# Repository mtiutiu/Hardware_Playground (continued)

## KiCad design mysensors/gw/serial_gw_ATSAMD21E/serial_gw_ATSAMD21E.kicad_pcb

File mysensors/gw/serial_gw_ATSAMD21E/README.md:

## Mysensors RFM69W Serial Gateway(ATSAMD21E)

**IMPORTANT NOTICE: this project proved not to work - Found the issue - VDDCORE was tied to the 3.3V supply rail by accident! - Fixed in REV 0.5**

##### 3D renderings of pcb

Top view | Bottom view
------------ | -------------
 | 

**Description:**

This is a Mysensors serial GW using **RFM69W** radio module and **ATSAMD21E** 32 bit MCU 

**Key features:**

 - **ATSHA204A** for signing
 - **MySensors** ready(ATSAMD21E + RFM69W)

**Work progress:**
 1. Test/verify the pcb board correctness(from both electrical and mechanical point of views) - **DONE**
 2. Produce the initial PCB's using some external PCB manufacturer - **IN PROGRESS**
 3. Components assembly(soldering)
 4. Upload Mysensors serial GW sketch code
 5. Verify the real board with running code
 6. Create project enclosure using a 3D printer

**HW Revisions:**
 - 0.1 - initial design
 - 0.2 - added I2C EEPROM and VUSB filtering caps
 - 0.3 - added USB lines termination resistors
 - 0.4 - added I2C EEPROM pull-up resistors
 - 0.5 - fixed VDDCORE mistake

**Credits:**
  
  All credits go to **MySensors** team for the great work and to the opensource community

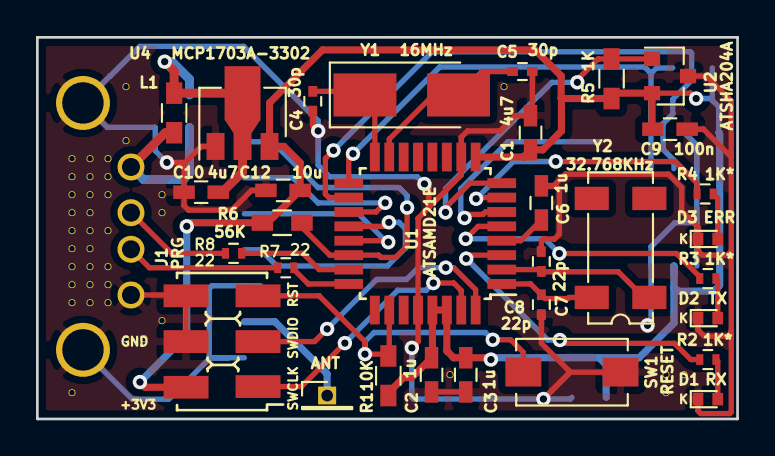
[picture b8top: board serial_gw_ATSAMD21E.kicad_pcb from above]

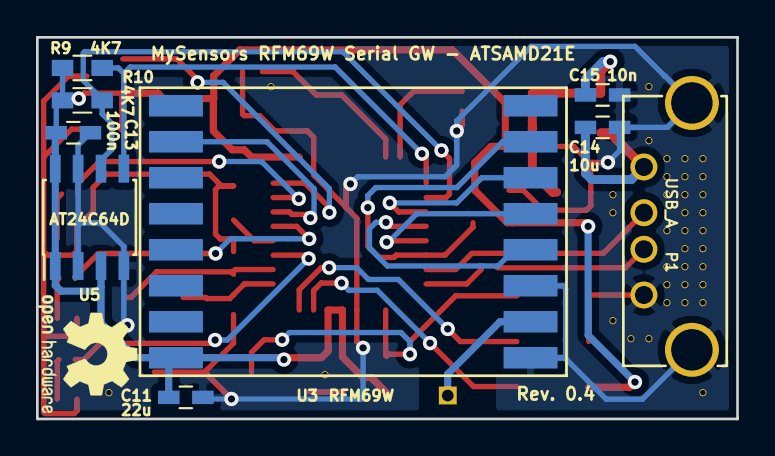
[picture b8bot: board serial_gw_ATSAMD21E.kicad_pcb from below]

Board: 2 copper layers, 38.9 x 21.2 mm, 78 parts (8 on the bottom side), 31 nets.

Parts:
C1, C10: 4u7; C_0603_HandSoldering
C2, C3, C6: 1u; C_0603_HandSoldering
C4, C5: 30p; C_0402
C7, C8: 22p; C_0402
C9, C13: 100n; C_0603_HandSoldering
C11: 22u; C_0603_HandSoldering
C12, C14: 10u; C_0603_HandSoldering
C15: 10n; C_0603_HandSoldering
D1: RX; LED_0402
D2: TX; LED_0402
D3: ERR; LED_0402
J1: PRG; AVR_ISP_SMT_Small_02x03
L1: BLM18HE152SN1D; R_0603_HandSoldering
P1: USB_A; USB_A_bottom
P2: ANT; Pin_Header_Straight_1x01_Pitch1.27mm
R1: 10K; R_0603_HandSoldering
R2, R3, R4: 1K*; R_0402
R5: 1K; R_0603_HandSoldering
R6: 56K; R_0603_HandSoldering
R7, R8: 22; R_0402
R9, R10: 4K7; R_0603_HandSoldering
SW1: RESET; SW_SPST_EVQPE1
U1: ATSAMD21E; TQFP-32_7x7mm_Pitch0.8mm
U2: ATSHA204A; SOT-23
U3: RFM69W; RFM69HW_SMD_Handsoldering
U4: MCP1703A-3302; SOT89-3_Housing
U5: AT24C64D; SOIC-8_3.9x4.9mm_Pitch1.27mm
V2_7, V2_8, V2_9, V2_10, V2_11, V2_12, V2_13, V2_14, V2_15, V2_20, V3_7, V3_8, V3_9, V3_10, V3_11, V3_12, V3_13, V3_14, V3_15, V4_7, V4_8, V4_9, V4_11, V4_13, V4_14, V4_15, V5_3, V5_6, V5_17, V6_17, V7_9, V7_10, V7_16, V23_19, V26_3, V35_19, V35_20, V36_19: AUTO_VIA; VIA_MATRIX
Y1: 16MHz; Crystal_SMD_5032-2pin_5.0x3.2mm_HandSoldering
Y2: 32.768KHz; Crystal_SMD_SeikoEpson_MC306-4pin_8.0x3.2mm

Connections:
+3V3: C1.1, C2.2, C3.1, C9.1, C11.1, C12.1, C13.1, J1.2, R1.2, R5.2, R6.2, R9.2, R10.2, U1.9, U1.29, U1.30, U2.2, U3.8, U4.3, U5.1, U5.3, U5.8
/ATSHA204A: R5.1, U1.8, U2.1
/GW_ERR_LED: R4.2, U1.7
/GW_RX_LED: R2.2, U1.3
/GW_TX_LED: R3.2, U1.5
/MISO: U1.21, U3.13
/MOSI: U1.19, U3.14
/RFM69W_INT: U1.6, U3.2
/RFM69W_SS: R6.1, U1.22, U3.15
/RST: J1.5, R1.1, SW1.1, U1.26
/SCK: U1.20, U3.12
/SCL: R10.1, U1.18, U5.6
/SDA: R9.1, U1.17, U5.5
/SWCLK: J1.1, U1.31
/SWDIO: J1.3, U1.32
/USBDM: R8.1, U1.23
/USBDP: R7.1, U1.24
/VBUS: C10.1, C15.2, L1.2, U4.2
GND: C1.2, C2.1, C3.2, C4.2, C5.2, C6.2, C7.2, C8.2, C9.2, C10.2, C11.2, C12.2, C13.2, C14.1, C15.1, D1.1, D2.1, D3.1, J1.4, J1.6, P1.4, P1.5, SW1.2, U1.10, U1.28, U2.3, U3.9, U3.11, U4.1, U5.2, U5.4, U5.7, V2_7.1, V2_8.1, V2_9.1, V2_10.1, V2_11.1, V2_12.1, V2_13.1, V2_14.1, V2_15.1, V2_20.1, V3_7.1, V3_8.1, V3_9.1, V3_10.1, V3_11.1, V3_12.1, V3_13.1, V3_14.1, V3_15.1, V4_7.1, V4_8.1, V4_9.1, V4_11.1, V4_13.1, V4_14.1, V4_15.1, V5_3.1, V5_6.1, V5_17.1, V6_17.1, V7_9.1, V7_10.1, V7_16.1, V23_19.1, V26_3.1, V35_19.1, V35_20.1, V36_19.1
unnamed: C4.1, U1.16, Y1.1
unnamed: C5.1, U1.15, Y1.2
unnamed: C6.1, U1.4
unnamed: C7.1, U1.2, Y2.1
unnamed: C8.1, U1.1, Y2.4
unnamed: C14.2, L1.1, P1.1
unnamed: D1.2, R2.1
unnamed: D2.2, R3.1
unnamed: D3.2, R4.1
unnamed: P1.2, R8.2
unnamed: P1.3, R7.2
unnamed: P2.1, U3.10

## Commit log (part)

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2017-02-06 cleanups
2017-02-07 [mysensors heater_node] added 3d enclosure design
2017-02-08 added cr123 node gerbers zip file
2017-02-13 [mysensors livolo_EU_switch node] removed touch pads solder paste
2017-02-14 [mysensors serial_gw] fixed usb A connector position
2017-02-14 fixed schematics due to kicad libraries changes
2017-02-14 [mysensors serial_gw] fixed enclosure design based on usb A connector changes
2017-02-14 [mysensors serial_gw] removed capacitor from reset switch as it interferes with arduino serial bootloader
2017-02-14 [mysensors serial_gw/heater] removed capacitor from reset switch as it interferes with arduino serial bootloader
2017-02-14 [mysensors serial_gw] enclosure - leave more space for the reset switch
2017-02-15 [mysensors serial_gw] improved 3.3V power supply line routing for the radio module
2017-02-15 [mysensors serial_gw] lifted leds 3 models a little bit on the z axis so that the board model is exported properly
2017-02-15 stl models updates
2017-02-16 [mysensors heater_node] pcb updates regarding drill holes
2017-02-16 enclosure design updates
2017-02-21 updated projects enclosures
2017-02-22 [mysensors livolo_EU_switch] fixed board outline dimensions
2017-02-22 [mysensors livolo_EU_switch] updated 3d renderings
2017-02-22 [mysensors livolo_EU_switch] moved step-down converter inductance a little bit of the board margin - updated pcb/gerbers
2017-02-22 [mysensors livolo_EU_switch] updated gerbers zip file
2017-02-24 added more sensors to cr2032 node and renamed project
2017-02-24 [mysensors multisensor_CR2032] updated renderings and readme
2017-02-28 [livolo_EU_switch] fixed leds orientation and added touch pads silkscreen
2017-02-28 lock mounting holes on all pcbs
2017-03-02 added esp12-e module
2017-03-02 [sd_wav_pcm5100] small pcb refactorings
2017-03-06 refactorings
2017-03-09 added atsamd21e serial gw
2017-03-09 [livolo_EU_switch] added ferrite bead and removed reset pin capacitor
2017-03-09 [serial_gw_ATSAMD21E] renewed pdf schematic
2017-03-09 [livolo_EU_switch] fixed some pcb tracks looking ugly
2017-03-10 pcb refactorings - atsamd gw & livolo eu switch
2017-03-10 pcb refactorings - atsamd gw
2017-03-10 added projects fplib table
2017-03-13 [livolo_EU_switch] reverted to mic5205 ldo vreg
2017-03-13 [livolo_EU_switch] added tantalum caps in the final power stage for better stability
2017-03-15 [heater node] fixed enclosure
2017-03-17 [serial_gw_ATSAMD21E] added enclosure stl files
2017-03-17 [mysensors serial_gw_ATMEGA328P] added ferrite bead for EMI suppression
2017-03-20 [serial_gw_ATSAMD21E] added I2C EEPROM and VUSB filtering caps
2017-03-20 [serial_gw_ATSAMD21E] some final pcb touches
2017-03-21 [serial_gw_ATSAMD21E] removed wrl models reference
2017-03-21 mysensors serial gw's refactorings
2017-03-21 [serial_gw_ATSAMD21E] pcb refactorings
2017-03-22 added usb termination resistors for all usb based projects
2017-03-23 [multisensor_CR2032] added a3212 hall sensor support
2017-03-23 [multisensor_CR2032] small pcb estetic refactorings
2017-03-27 [led_strip_actuator] added hw design files
2017-03-27 [led_strip_actuator] pcb estetic refactorings
2017-03-27 [led_strip_actuator] replaced wrl references with stp in the kicad pcb file
2017-03-28 [led_strip_actuator] added relay voltage selector jumpers
2017-03-28 pcb refactorings
2017-03-28 [led_strip_actuator] added enclosure design files
2017-03-28 [led_strip_actuator] 3d renderings refactorings
2017-03-28 projects structure/naming refactorings
2017-03-28 [mysensors][minimal_node] initial hw design
2017-03-30 added new kicad libs in
2017-03-30 updated projects fp lib table
2017-04-03 renamed livolo eu switch project properly
2017-04-03 fixed fp-lib-table
2017-04-04 [mysensors][livolo_EU_switch][VL-C700X-1_Ver_B8]fixed radio filtering capacitor orientation
2017-04-04 [mysensors][livolo_EU_switch][VL-C700X-1_Ver_B8]fixed renderings
2017-04-04 [mysensors][livolo_EU_switch][VL-C702X-2_Ver_C1] initial draft
2017-04-07 added esp modules and some livolo wifi schematic draft
2017-04-07 added some extra docs
2017-04-13 [wifi draft] added esp12-f/e footprints
2017-04-13 [wifi draft] added right footprints for polarized capacitors
2017-05-02 fixed fplib table files and atsamd21 serial gw usb connector placement
2017-05-02 [mysensors][serial_gw_ATSAMD21E] fixed enclosure
2017-05-03 [mysensors][ws281x_led_strip_controller] initial commit
2017-05-04 [mysensors][ws281x_led_strip_controller] increased power supply positive rail width for 9A max
2017-05-04 [mysensors][ws281x_led_strip_controller] pcb estetic touches
2017-05-04 [mysensors][minimal_node] pcb estetic touches
2017-05-04 added dxf for new livolo switche
2017-05-05 [mysensors][livolo_EU_switch][VL-C702X-2_Ver_C1] some pcb estetic touches
2017-05-05 [mysensors] livolo EU switch nodes proper naming
2017-05-08 [mysensors][livolo_EU_switch][VL-C700X-1_Ver_C2] pcb refactorings
2017-05-08 restructured livolo switches folders
2017-05-08 [mysensors][livolo_EU_switch][VL-C700X-1_Ver_C2][1_channel] initial draft
2017-05-08 [mysensors][livolo_EU_switch][VL-C700X-1_Ver_C2] pcb refactorings for both 1 & 2 channel variant
2017-05-09 [mysensors]livolo switch nodes - pcb refactorings
2017-05-09 [mysensors][livolo_EU_switch][VL-C700X-1_Ver_C2][2_channel] moved the spi flash chip away from the pcb margins a little bit
2017-05-09 [mysensors][livolo_EU_switch][VL-C700X-1_Ver_C2][1_channel] pcb estetic touches
2017-05-10 [mysensors][livolo_EU_switch][VL-C700X-1_Ver_C2][1_channel] tied up relay channels cmd pins as there's only one
2017-05-16 [mysensors][arduino_shield][uno] initial commit
2017-05-18 [mysensors][arduino_shield][uno] fixed fp lib table file
2017-05-24 [mysensors][gw][serial_gw_ATSAMD21E] added i2c eeprom pull-up resistors
2017-05-29 [mysensors][node][ws281x_led_strip_controller] replaced atmega328p with atmega644p for more ram/flash
2017-05-29 [mysensors][node][ws281x_led_strip_controller] pcb refactorings
2017-06-07 [mysensors][node][ws281x_led_strip_controller] added proper via stitching
2017-06-12 added proper via stitching to all boards
2017-06-13 projects refactorings
2017-06-20 [mysensors][node] nrf51822 variant pcb final touches
2017-06-21 added ptr5518 3d model
2017-06-27 [mysensors] added livolo nrf51822 1 channel variant
2017-06-27 [mysensors] livolo nrf51822 2 channel variant final touches
2017-07-05 new stuff
2017-07-05 nrf51822 important note added
2017-07-11 livolo nrf51822 - switched to mtch105 touch sensor and improved pcb
2017-07-13 final touches for livolo eu switch nrf51822 2 ch variant
2017-07-14 wifi draft - switched buck converter to mcp16301
2017-07-18 added maple mini serial gw for mysensors project
2017-07-18 oval pads for maple mini footprint as it allows tracks easily between
2017-07-19 serial_gw maple_mini final touches
2017-07-19 serial_gw maple_mini - oops! forgot to connect common ground
2017-07-19 serial_gw maple_mini - radio module 1mm holes
2017-07-19 serial_gw maple_mini - added enclosure and leds
2017-07-19 water leak detector node - initial commit
2017-07-20 updated projects fp-lib table
2017-07-20 added E73-2G4M04S symbol/footprint
2017-07-25 added WT51822-S4AT module, refactorings...
2017-07-25 mysensors water leak node - added nrf51822 module
2017-07-26 livolo EU switch nrf5 - final touches
2017-07-27 mysensors nrf5 livolo node one channel - final touches
2017-07-28 livolo_EU_switch/VL-C700X-1_Ver_C2_NRF51822/1_channel - final touches
2017-08-24 added espeasy wifi lights initial design
2017-08-24 wifi lights espeasy node - hardware 1st iteration
2017-08-24 wifi lights espeasy node - hardware design 2nd iteration
2017-08-24 wifi lights espeasy node - hardware design 3rd iteration
2017-08-25 wifi lights espeasy node - hardware design 4th iteration
2017-08-28 espeasy wifi lights - final touches
2017-08-29 added wemos d1 mini stl
2017-08-31 refactorings - nrf24l01 livolo node
2017-09-02 restructuring project folders for livolo
2017-09-02 drc fix for nrf24l01 livolo_2_channels_1way_eu_switch
2017-09-02 pcb estetic touches - nrf24l01 livolo_2_channels_1way_eu_switch
2017-09-05 VL-C700X-1_Ver_C2/NRF24L01 2_channel - pcb final touches
2017-09-07 new symbols/footprints
2017-09-26 fixed projects according to latest kicad libs changes
2017-10-02 livolo nrf51822 refactorings
2017-10-10 rpi zero w node
2017-10-10 bla bla
2017-10-10 rpi zero mys ble node refactorings
2017-10-11 rpi zero mys-ble refactorings
2017-10-11 nrf51822 livolo 2 ch node gerber regenerated
2017-10-12 refactored all kicad projects due to kicad latest library changes
2017-10-13 livolo eu switch - nrf24l01 1 channel variant
2017-10-13 livolo eu switch - nrf24l01 1 channel variant refactorings
2017-10-16 orange pi zero shield refactorings
2017-10-16 livolo nrf51822 boards refactorings, opi zero
2017-10-19 livolo nrf5xxx small refactorings
2017-11-20 added nanopi duo symbol/footprint
2018-01-08 nanopi duo usb shield
2018-01-11 nano pi duo usb shield finish ups
2018-01-11 nano pi duo usb shield pdf schematic
2018-01-12 nano pi duo usb shield - stitching vias
2018-01-30 added esp8266 in arduino uno format - initial draft
2018-01-31 added esp8266 in arduino uno format - hw design 2nd pass
2018-01-31 added esp8266 in arduino uno format - hw design 3rd pass
2018-01-31 added esp8266 in arduino uno format - hw design 4th pass
2018-01-31 added esp8266 in arduino uno format - hw design 5th pass
2018-01-31 added esp8266 in arduino uno format - hw design 6th pass
2018-02-01 added esp8266 in arduino uno format - hw design 7th pass
2018-02-02 added esp8266 in arduino uno format - hw design final pass
2018-02-02 added esp8266 in arduino uno format - hw design final touches
2018-02-05 esp8266 uno - added 30A relay shield hw design
2018-02-06 esp8266 uno relay shield - added toner transfer variant
2018-02-06 project folders restructuring
2018-02-07 esp8266 uno refactorings
2018-02-07 esp8266 uno - fixed input diode orientation
2018-02-12 esp8266 uno relay shield fixes
2018-02-14 added esp8266 to rfm69w adapter
2018-02-14 esp8266 to rfm69w adapter refactorings
2018-02-14 esp8266 to rfm69 adapter refactorings
2018-02-15 esp8266 rfm69w adapter refactorings
2018-02-16 esp8266 relay shield refactorings
2018-02-19 projects libs fixes
2018-02-20 added esp8266 based ws2812fx controller
2018-02-20 esp8266 ws2812fx controller refactorings
2018-02-21 esp8266 - added heater actuator project
2018-02-21 esp8266 heater actuator refactorings
2018-02-23 added mysensors pro mini board
2018-02-23 mysensors pro mini board - more renderings
2018-02-23 mys pro mini refactorings
2018-03-20 HV buck led driver experiment
2018-03-27 led driver refactorings
2018-03-30 lm317 adj supply - initial commit
2018-04-02 lm317 adj supply - final touches
2018-05-18 added 3dshapes to projects
2018-05-18 fixed 3dshapes reference
2018-05-25 added Holyiot-NRF52832 module
2018-05-28 livolo eu switch 1 channel nrf52832 variant(holyiot module)
2018-05-28 livolo eu switch 1 channel nrf52832 refactorings
2018-05-28 livolo eu switch 1 channel nrf52832 rev. 0.2
2018-05-29 make other projects standalone
2018-05-29 converted projects to work with kicad sym-lib-table new mechanism
2018-06-07 livolo eu switch - holyiot nrf52 module footprint and board small fixes
2018-06-26 added CYBLE-012012-10 module and symbol
2018-06-26 added cyble based livolo 2ch EU plate
2018-06-28 livolo eu switch 2 ch cyble final touches
2018-07-10 added cyble livolo 1 channel module
2018-08-08 added esp32 footprint
2018-08-08 added rpi zero ws2812 shield
2018-11-21 nrf52 2 ch board for livolo
2018-11-21 nrf52x livolo 2ch silkscreen fix
2018-12-07 submodules updates
2019-05-31 mys serial gw samd21 fix vddcore issue
2019-11-18 nrf52xxx livolo hw small refactorings, initial nrf52840 work...
2019-12-19 readme's update
2020-02-13 projects reorg, added custom power supply and front plates for in wall touch switch
2020-02-13 added touch pads silkscreen
2020-02-14 new projects ported from EasyEDA
2020-03-23 [touch switch] added model files for 3d printing
2020-10-15 bl prj update
2020-10-31 nrf52840 switches - initial commit
2020-10-31 added full NRF52840 design, changed some names
2020-10-31 reverted name change
2020-11-21 final revision for E3 board
2021-01-07 eu switch rev0.4 - the last one
